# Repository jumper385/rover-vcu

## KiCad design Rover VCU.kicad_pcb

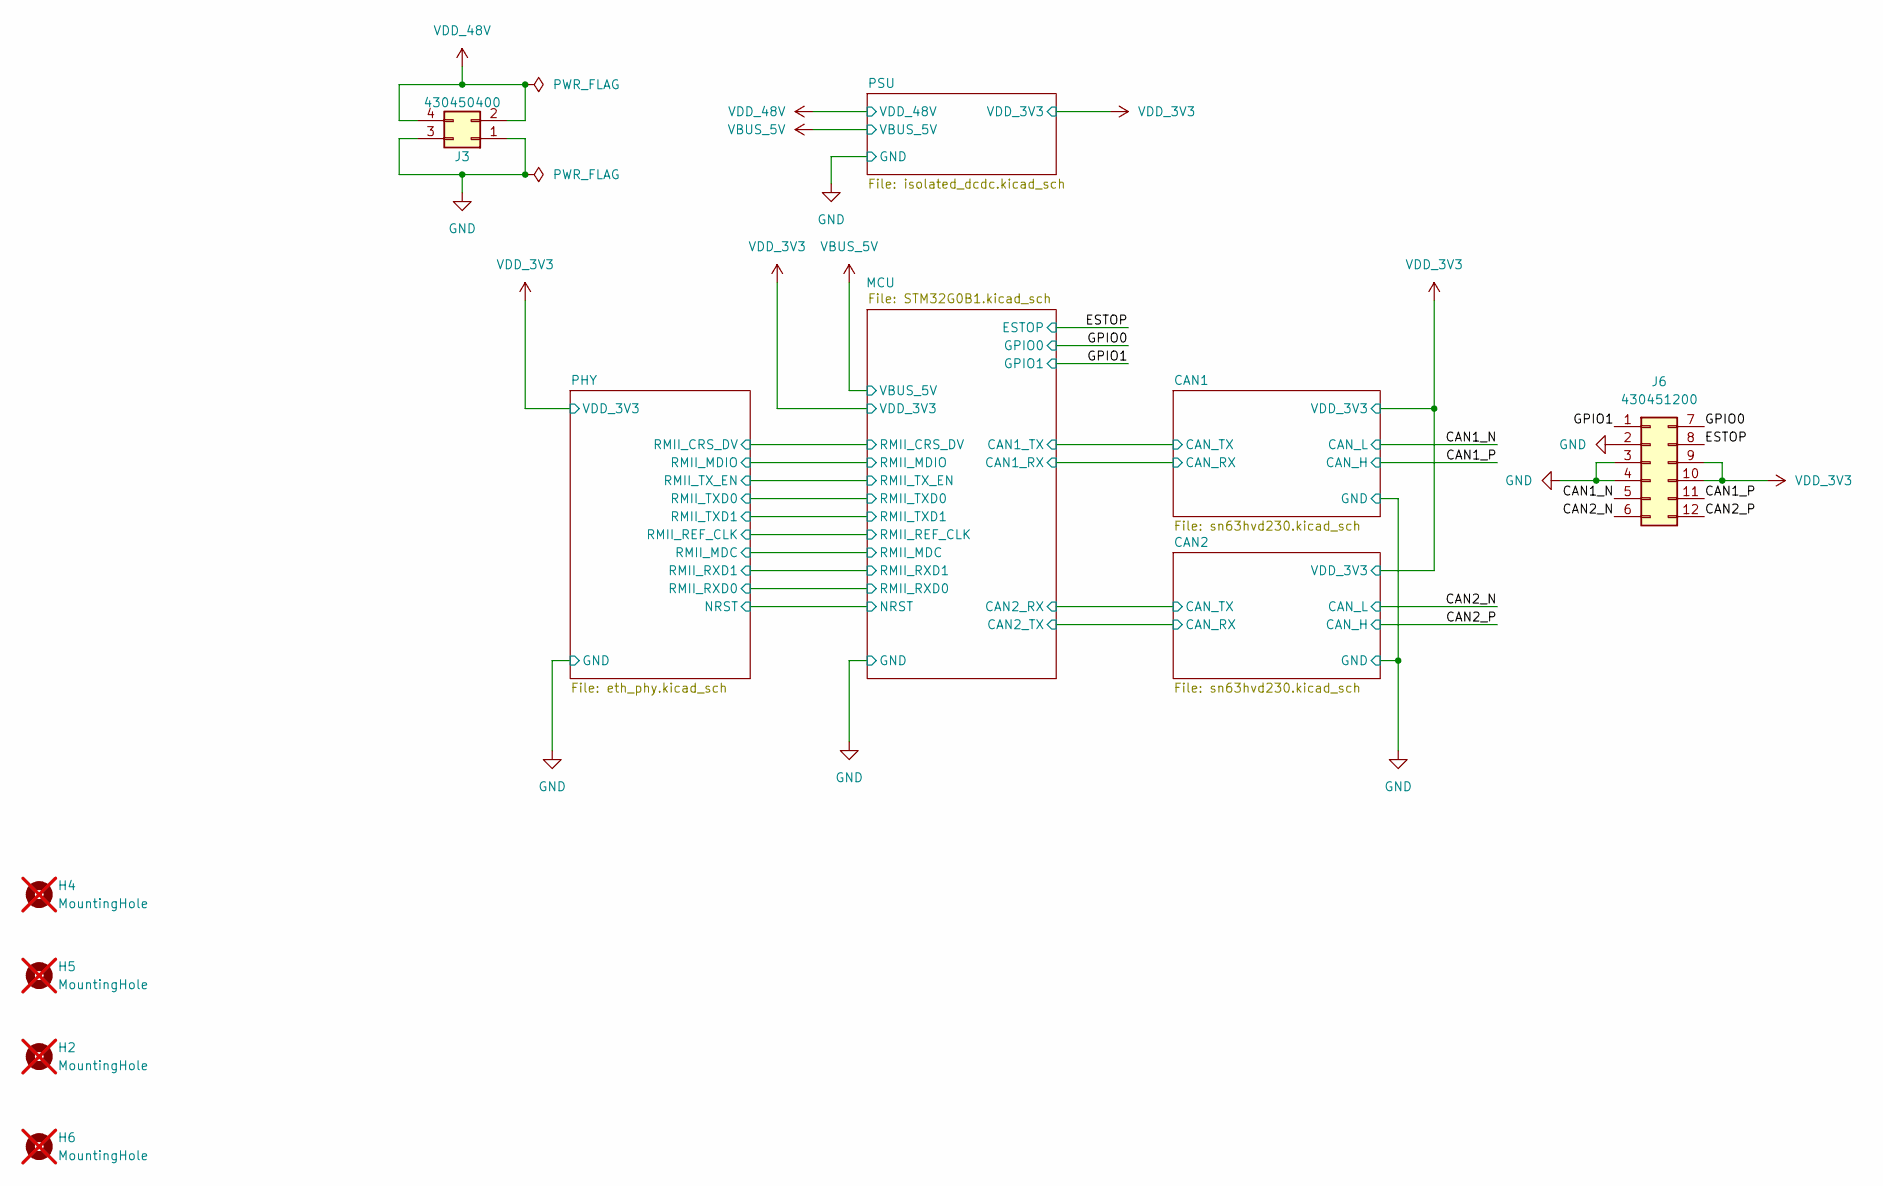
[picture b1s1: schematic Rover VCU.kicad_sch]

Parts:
H2, H4, H5, H6: MountingHole; MountingHole_3.2mm_M3; not fitted
J3: 430450400; Molex_Micro-Fit_3.0_43045-0400_2x02_P3.00mm_Horizontal; MFR_PN1 430450400; JLC_PN C122413
J6: 430451200; Molex_Micro-Fit_3.0_43045-1200_2x06_P3.00mm_Horizontal; MFR_PN1 430451200; JLC_PN C277636

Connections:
/CAN1_N: J6.5; also elsewhere on the board
/CAN1_P: J6.11; also elsewhere on the board
/CAN2_N: J6.6; also elsewhere on the board
/CAN2_P: J6.12; also elsewhere on the board
/ESTOP: J6.8; also elsewhere on the board
/GPIO0: J6.7; also elsewhere on the board
/GPIO1: J6.1; also elsewhere on the board
/VDD_3V3: J6.9, J6.10; also elsewhere on the board
/VDD_48V: J3.2, J3.4; also elsewhere on the board
GND: J3.1, J3.3, J6.2, J6.3, J6.4; also elsewhere on the board

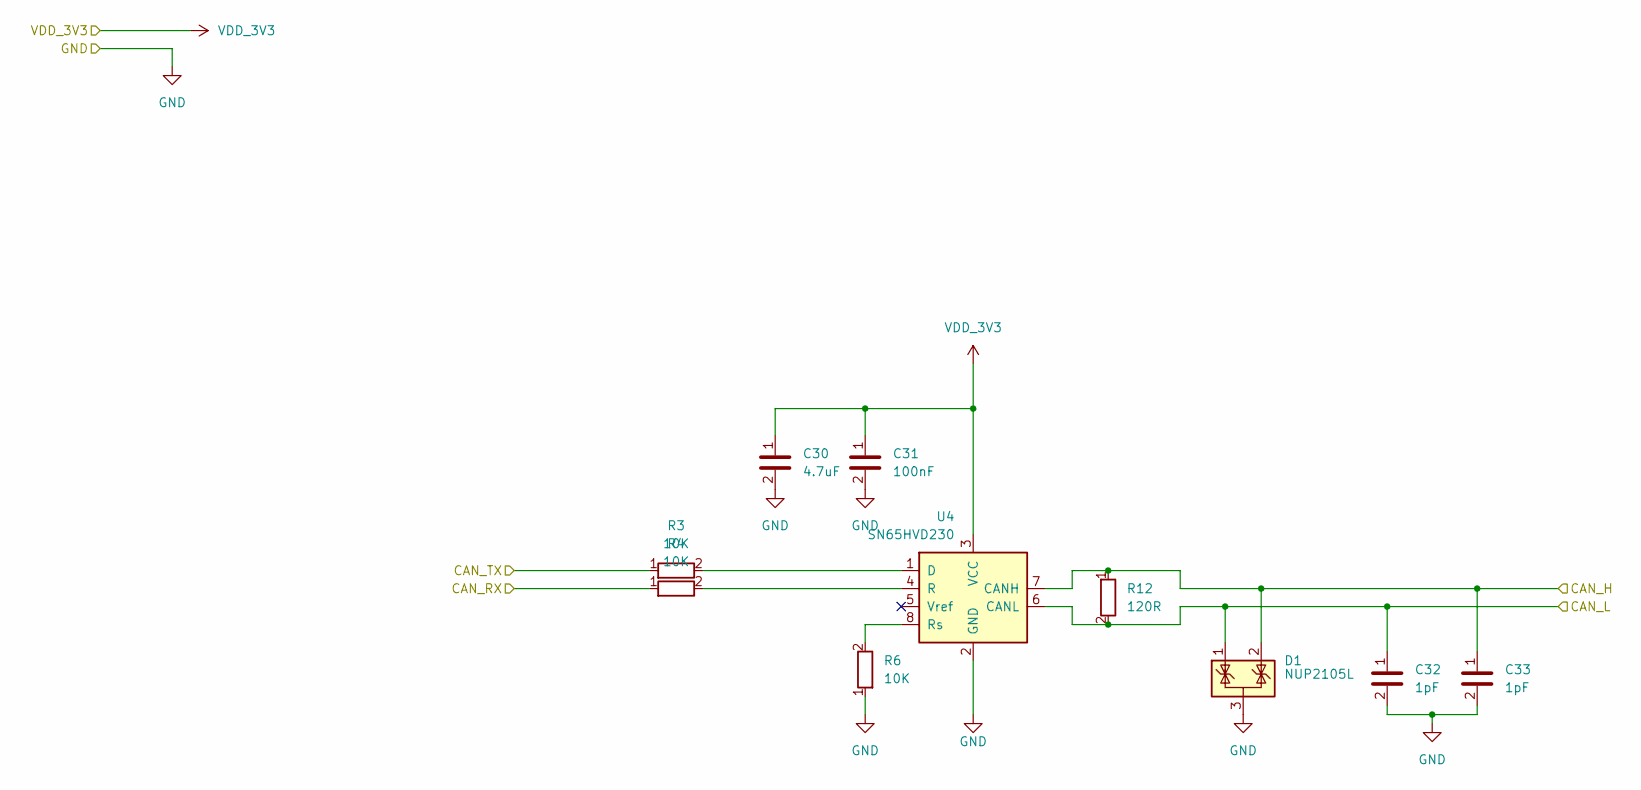
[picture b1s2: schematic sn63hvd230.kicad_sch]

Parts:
C30: 4.7uF; C_0402; Voltage Rating 10V; MFR_PN1 CL05A475MP5NRNC; JLC_PN C23733
C31: 100nF; C_0402; Voltage Rating 16V; MFR_PN1 CL05B104KO5NNNC; JLC_PN C1525
C32, C33: 1pF; C_0402; Voltage Rating 50V; MFR_PN1 0402CG1R0C500NT; JLC_PN C1550
D1: NUP2105L; SOT-23; MFR_PN1 NUP2105LT1G; JLC_PN C20617923
R3, R4, R6: 10K; R_0402; JLC_PN C25744
R12: 120R; R_0402; MFR_PN1 0402WGF1200TCE; JLC_PN C25079
U4: SN65HVD230; SOIC-8_3.9x4.9mm_P1.27mm; MFR_PN1 SN65HVD230DR; JLC_PN C12084

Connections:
/CAN1_N: C32.1, D1.1 (K), R12.2, U4.6 (CANL); also elsewhere on the board
/CAN1_P: C33.1, D1.2 (K), R12.1, U4.7 (CANH); also elsewhere on the board
/MCU/CAN1_RX: R4.1; also elsewhere on the board
/MCU/CAN1_TX: R3.1; also elsewhere on the board
/VDD_3V3: C30.1, C31.1, U4.3 (VCC); also elsewhere on the board
GND: C30.2, C31.2, C32.2, C33.2, D1.3 (A), R6.1, U4.2 (GND); also elsewhere on the board
unnamed: R3.2, U4.1 (D)
unnamed: R4.2, U4.4 (R)
unnamed: R6.2, U4.8 (Rs)

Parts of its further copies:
C34: 4.7uF; C_0402; Voltage Rating 10V; MFR_PN1 CL05A475MP5NRNC; JLC_PN C23733
C35: 100nF; C_0402; Voltage Rating 16V; MFR_PN1 CL05B104KO5NNNC; JLC_PN C1525
C36, C37: 1pF; C_0402; Voltage Rating 50V; MFR_PN1 0402CG1R0C500NT; JLC_PN C1550
D2: NUP2105L; SOT-23; MFR_PN1 NUP2105LT1G; JLC_PN C20617923
R7, R8, R9: 10K; R_0402; JLC_PN C25744
R13: 120R; R_0402; MFR_PN1 0402WGF1200TCE; JLC_PN C25079
U5: SN65HVD230; SOIC-8_3.9x4.9mm_P1.27mm; MFR_PN1 SN65HVD230DR; JLC_PN C12084

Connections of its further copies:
/CAN2_N: C36.1, D2.1 (K), R13.2, U5.6 (CANL); also elsewhere on the board
/CAN2_P: C37.1, D2.2 (K), R13.1, U5.7 (CANH); also elsewhere on the board
/MCU/CAN2_RX: R7.1; also elsewhere on the board
/MCU/CAN2_TX: R8.1; also elsewhere on the board
/VDD_3V3: C34.1, C35.1, U5.3 (VCC); also elsewhere on the board
GND: C34.2, C35.2, C36.2, C37.2, D2.3 (A), R9.1, U5.2 (GND); also elsewhere on the board
unnamed: R7.2, U5.1 (D)
unnamed: R8.2, U5.4 (R)
unnamed: R9.2, U5.8 (Rs)

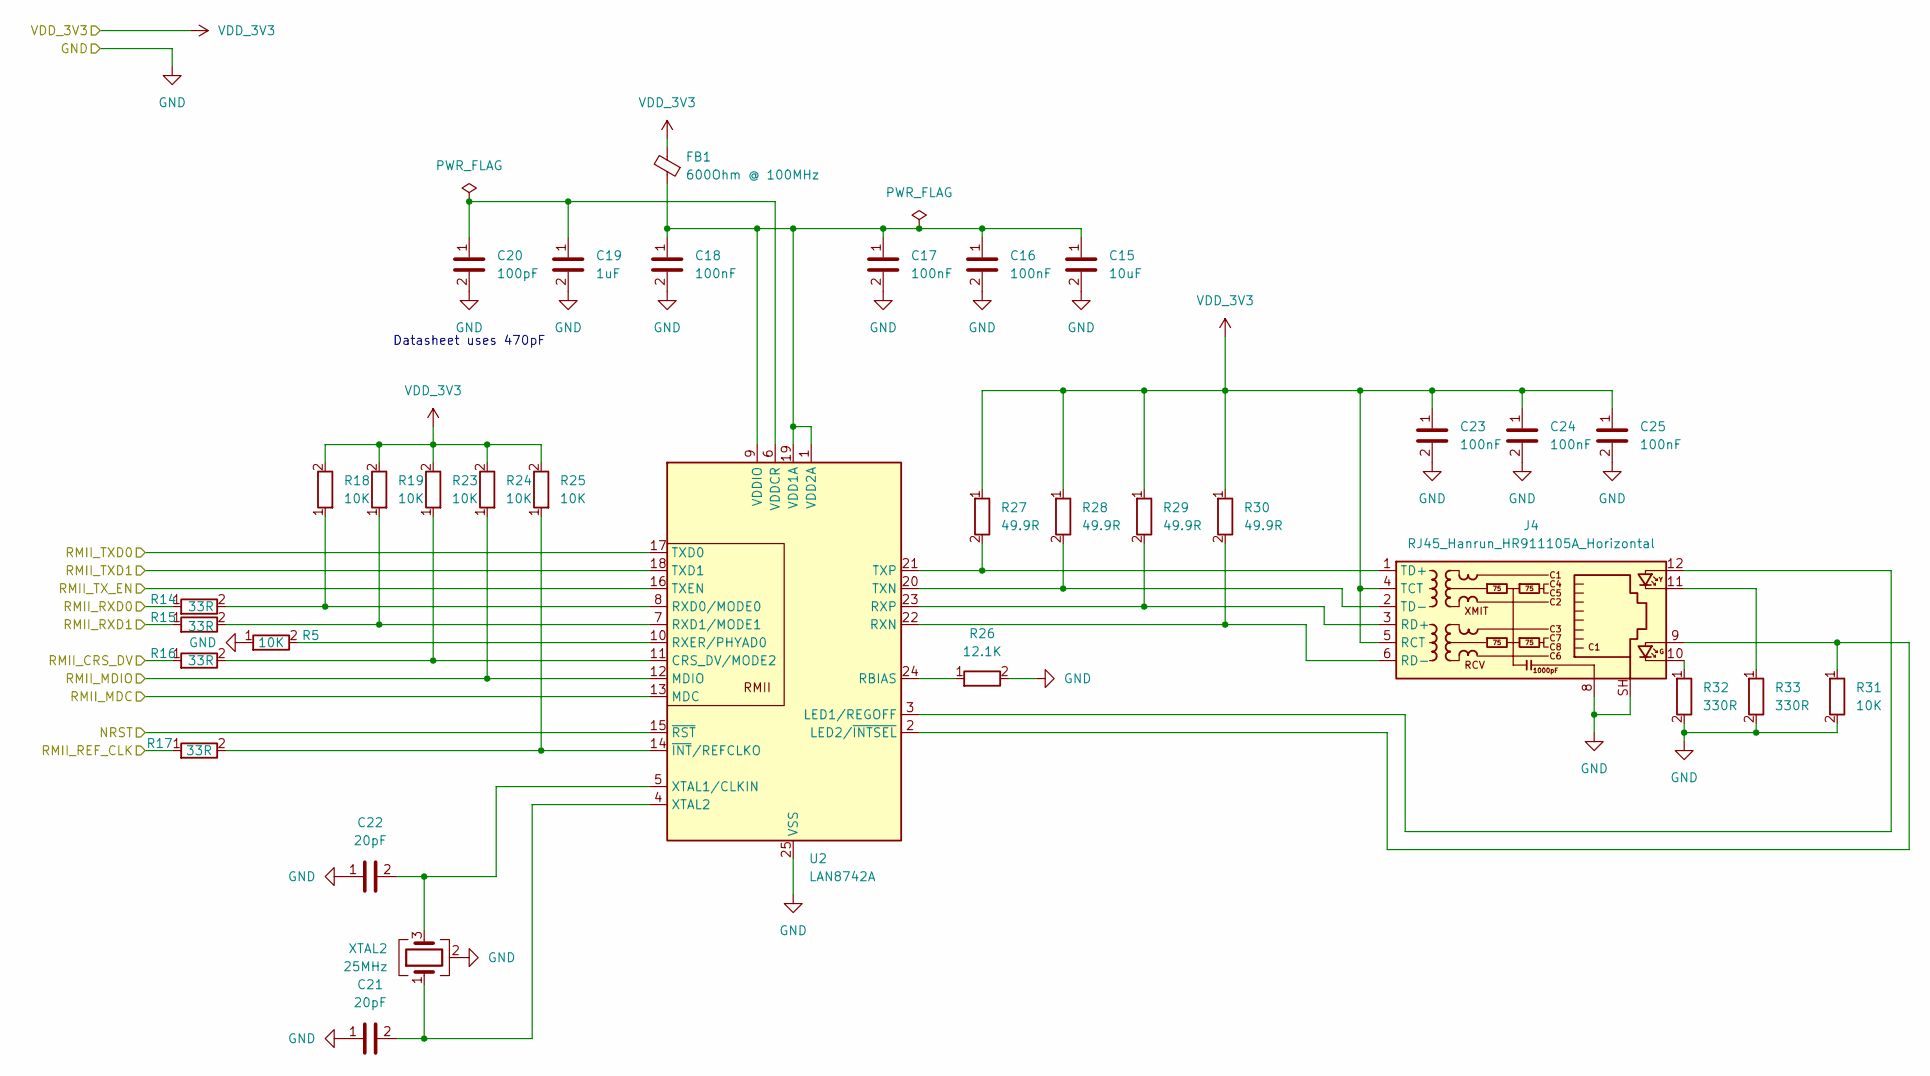
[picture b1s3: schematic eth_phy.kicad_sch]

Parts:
C15: 10uF; C_0402; Voltage Rating 6.3V; MFR_PN1 CL05A106MQ5NUNC; JLC_PN C15525
C16, C17, C18, C23, C24, C25: 100nF; C_0402; Voltage Rating 16V; MFR_PN1 CL05B104KO5NNNC; JLC_PN C1525
C19: 1uF; C_0402; Voltage Rating 25V; MFR_PN1 CL05A105KA5NQNC; JLC_PN C52923
C20: 100pF; C_0402; Voltage Rating 50V; MFR_PN1 0402CG101J500NT; JLC_PN C1546
C21, C22: 20pF; C_0402; Voltage Rating 50V; MFR_PN1 0402CG200J500NT; JLC_PN C1554
FB1: 600Ohm @ 100MHz; C_0603_1608Metric; MFR_PN1 BLM18KG601SH1D; JLC_PN C1002
J4: RJ45_Hanrun_HR911105A_Horizontal; MFR_PN1 HR911105A; JLC_PN C12074
R5, R18, R19, R23, R24, R25, R31: 10K; R_0402; JLC_PN C25744
R14, R15, R16, R17: 33R; R_0402; JLC_PN C25105
R26: 12.1K; R_0402; MFR_PN1 0805W8F1212T5E; JLC_PN C17431
R27, R28, R29, R30: 49.9R; R_0402; JLC_PN C25120
R32, R33: 330R; R_0402; JLC_PN C25104
U2: LAN8742A; VQFN-24-1EP_4x4mm_P0.5mm_EP2.5x2.5mm_ThermalVias; MFR_PN1 LAN8742AI-CZ-TR; JLC_PN C621425
XTAL2: 25MHz; Crystal_SMD_3225-4Pin_3.2x2.5mm; MFR_PN1 X322525MOB4SI; JLC_PN C9006

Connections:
/MCU/NRST: U2.15 (~RST); also elsewhere on the board
/MCU/RMII_CRS_DV: R16.1; also elsewhere on the board
/MCU/RMII_MDC: U2.13 (MDC); also elsewhere on the board
/MCU/RMII_MDIO: R24.1, U2.12 (MDIO); also elsewhere on the board
/MCU/RMII_REF_CLK: R17.1; also elsewhere on the board
/MCU/RMII_RXD0: R14.1; also elsewhere on the board
/MCU/RMII_RXD1: R15.1; also elsewhere on the board
/MCU/RMII_TXD0: U2.17 (TXD0); also elsewhere on the board
/MCU/RMII_TXD1: U2.18 (TXD1); also elsewhere on the board
/MCU/RMII_TX_EN: U2.16 (TXEN); also elsewhere on the board
/VDD_3V3: C23.1, C24.1, C25.1, FB1.2, J4.4 (TCT), J4.5 (RCT), R18.2, R19.2, R23.2, R24.2, R25.2, R27.1, R28.1, R29.1, R30.1; also elsewhere on the board
GND: C15.2, C16.2, C17.2, C18.2, C19.2, C20.2, C21.1, C22.1, C23.2, C24.2, C25.2, J4.8, J4.SH, R5.1, R26.2, R31.2, R32.2, R33.2, U2.25 (VSS), XTAL2.2 (G), XTAL2.4 (G); also elsewhere on the board
unnamed: J4.10, R32.1
unnamed: J4.11, R33.1
unnamed: J4.3 (RD+), R29.2, U2.23 (RXP)
unnamed: J4.6 (RD-), R30.2, U2.22 (RXN)
unnamed: J4.1 (TD+), R27.2, U2.21 (TXP)
unnamed: J4.2 (TD-), R28.2, U2.20 (TXN)
unnamed: R16.2, R23.1, U2.11 (CRS_DV/MODE2)
unnamed: J4.12, U2.3 (LED1/REGOFF)
unnamed: J4.9, R31.1, U2.2 (LED2/~INTSEL)
unnamed: R26.1, U2.24 (RBIAS)
unnamed: R14.2, R18.1, U2.8 (RXD0/MODE0)
unnamed: R15.2, R19.1, U2.7 (RXD1/MODE1)
unnamed: R5.2, U2.10 (RXER/PHYAD0)
unnamed: C15.1, C16.1, C17.1, C18.1, FB1.1, U2.1 (VDD2A), U2.9 (VDDIO), U2.19 (VDD1A)
unnamed: C19.1, C20.1, U2.6 (VDDCR)
unnamed: C22.2, U2.5 (XTAL1/CLKIN), XTAL2.3
unnamed: C21.2, U2.4 (XTAL2), XTAL2.1
unnamed: R17.2, R25.1, U2.14 (~INT/REFCLKO)

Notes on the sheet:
Datasheet uses 470pF

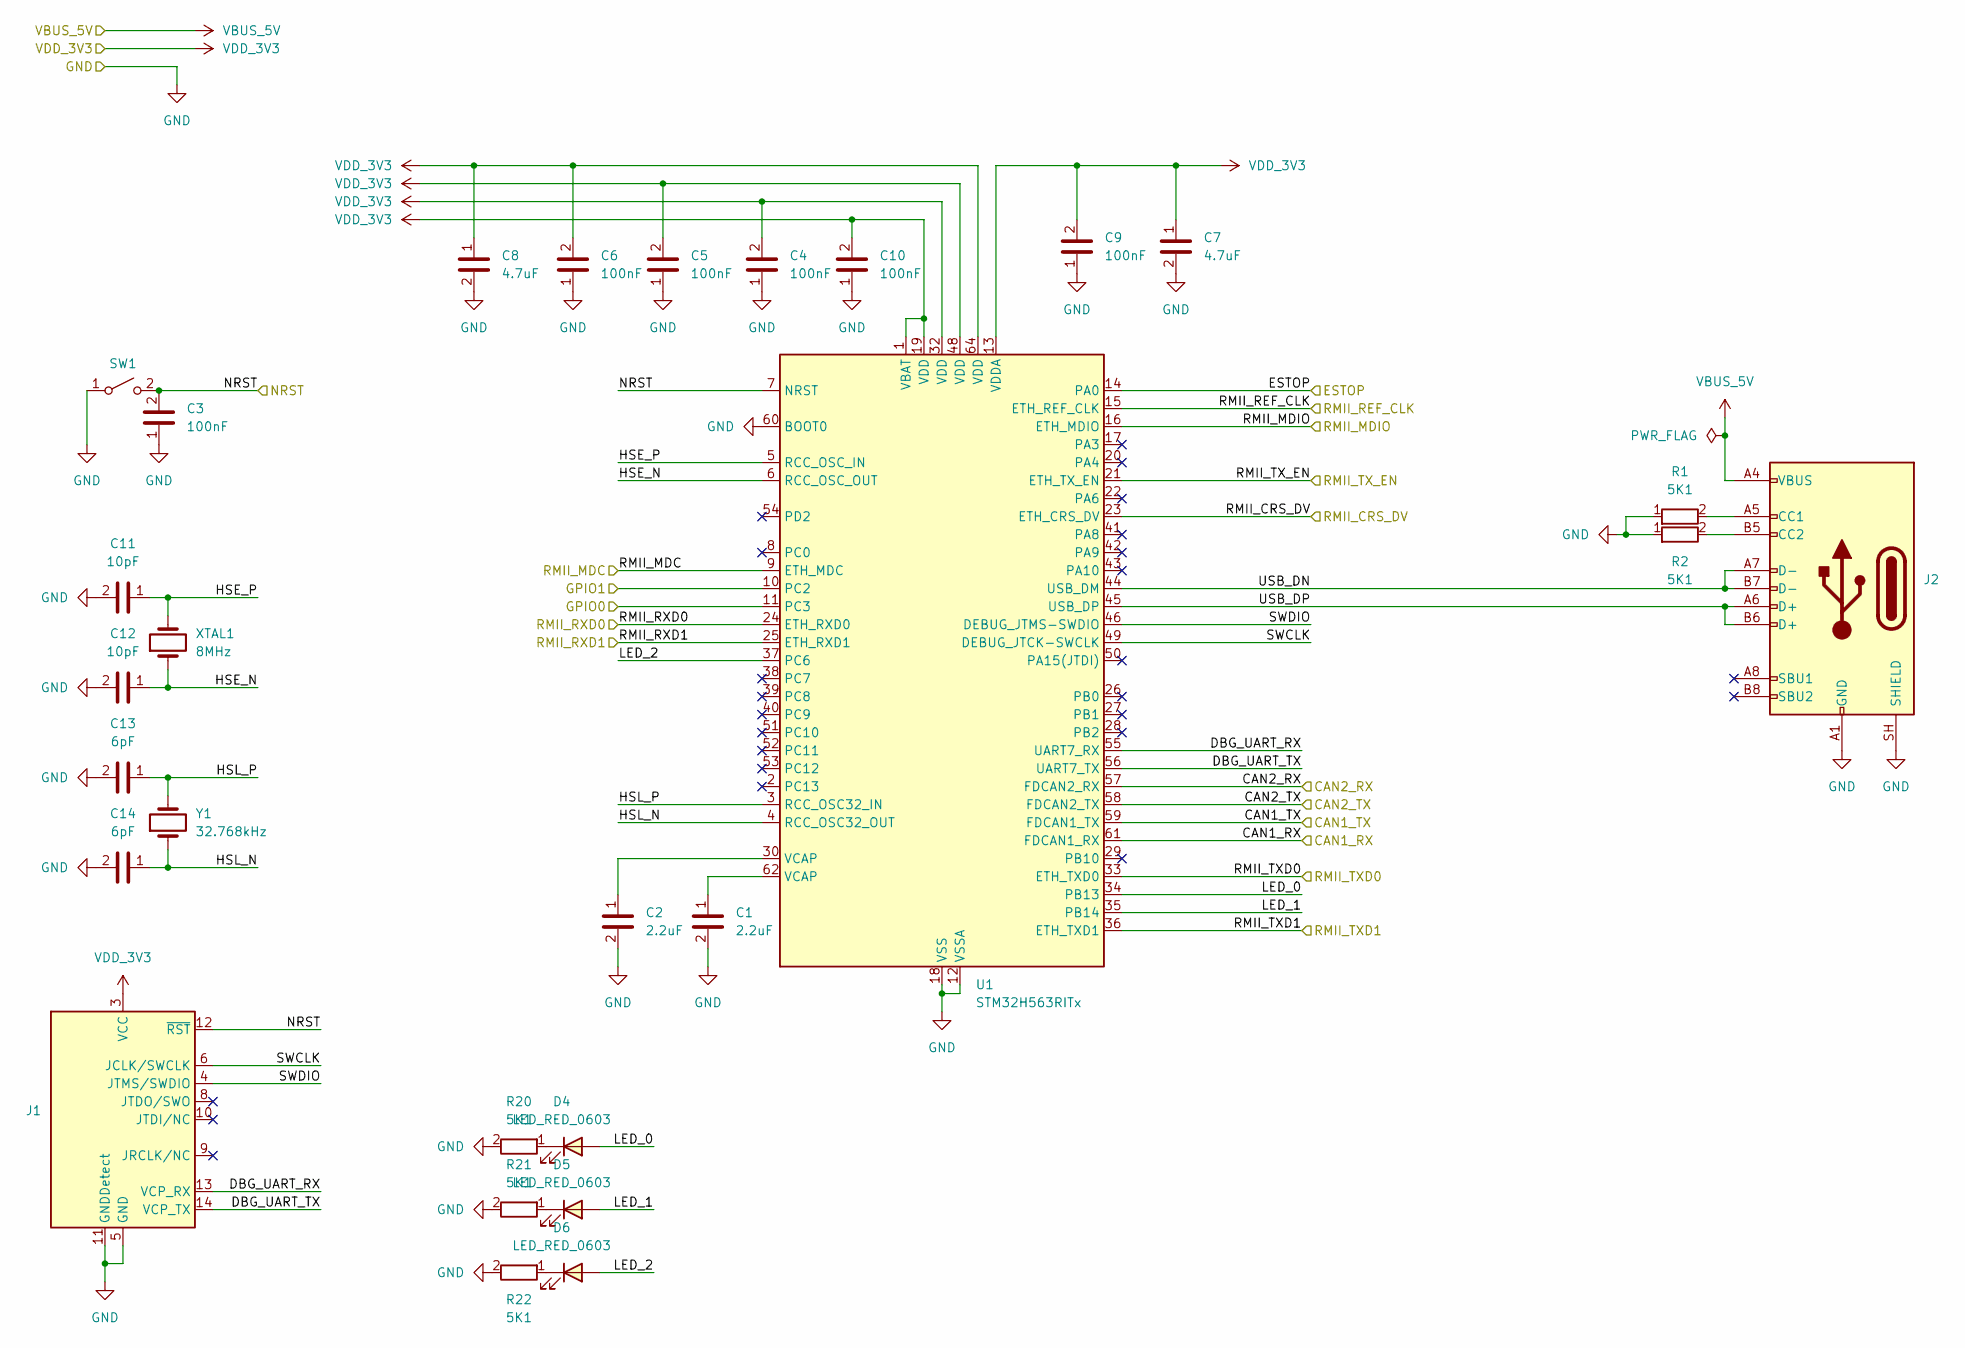
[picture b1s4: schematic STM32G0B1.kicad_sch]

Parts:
C1, C2: 2.2uF; C_0402; Voltage Rating 6.3V; MFR_PN1 CL05A225MQ5NSNC; JLC_PN C12530
C3, C4, C5, C6, C9, C10: 100nF; C_0402; Voltage Rating 16V; MFR_PN1 CL05B104KO5NNNC; JLC_PN C1525
C7, C8: 4.7uF; C_0402; Voltage Rating 10V; MFR_PN1 CL05A475MP5NRNC; JLC_PN C23733
C11, C12: 10pF; C_0402; Voltage Rating 50V; MFR_PN1 CL05C100JB5NNNC; JLC_PN C32949
C13, C14: 6pF; C_0402; Voltage Rating 50V; MFR_PN1 0402CG6R0C500NT; JLC_PN C30274
D4, D5, D6: LED_RED_0603; LED_0603_1608Metric; MFR_PN1 IN-S63FTHIR; JLC_PN C2286
J1: Conn_ST_STDC14; PinHeader_2x07_P1.27mm_Vertical_SMD; MFR_PN1 3220-14-0100-00; JLC_PN C27985148
J2: USB4105-GF-A; USB_C_Receptacle_GCT_USB4105-xx-A_16P_TopMnt_Horizontal; MFR_PN1 USB4105-GF-A; JLC_PN C393939
R1, R2, R20, R21, R22: 5K1; R_0402; JLC_PN C25905
SW1: TS-1088-AR02016; SW_SPST_TS-1088-xR020; MFR_PN1 C720477
U1: STM32H563RITx; LQFP-64_10x10mm_P0.5mm; JLC_PN C20619634
XTAL1: 8MHz; Crystal_SMD_5032-2Pin_5.0x3.2mm; MFR_PN1 X50328MSB2GI; JLC_PN C115962
Y1: 32.768kHz; Crystal_SMD_3215-2Pin_3.2x1.5mm; MFR_PN1 Q13FC13500004; JLC_PN C32346

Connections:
/ESTOP: U1.14 (PA0); also elsewhere on the board
/GPIO0: U1.11 (PC3); also elsewhere on the board
/GPIO1: U1.10 (PC2); also elsewhere on the board
/MCU/CAN1_RX: U1.61 (FDCAN1_RX); also elsewhere on the board
/MCU/CAN1_TX: U1.59 (FDCAN1_TX); also elsewhere on the board
/MCU/CAN2_RX: U1.57 (FDCAN2_RX); also elsewhere on the board
/MCU/CAN2_TX: U1.58 (FDCAN2_TX); also elsewhere on the board
/MCU/DBG_UART_RX: J1.13 (VCP_RX), U1.55 (UART7_RX)
/MCU/DBG_UART_TX: J1.14 (VCP_TX), U1.56 (UART7_TX)
/MCU/HSE_N: C12.1, U1.6 (RCC_OSC_OUT), XTAL1.1
/MCU/HSE_P: C11.1, U1.5 (RCC_OSC_IN), XTAL1.2
/MCU/HSL_N: C14.1, U1.4 (RCC_OSC32_OUT), Y1.1
/MCU/HSL_P: C13.1, U1.3 (RCC_OSC32_IN), Y1.2
/MCU/LED_0: D4.2 (A), U1.34 (PB13)
/MCU/LED_1: D5.2 (A), U1.35 (PB14)
/MCU/LED_2: D6.2 (A), U1.37 (PC6)
/MCU/NRST: C3.2, J1.12 (~RST), SW1.2 (B), U1.7 (NRST); also elsewhere on the board
/MCU/RMII_CRS_DV: U1.23 (ETH_CRS_DV); also elsewhere on the board
/MCU/RMII_MDC: U1.9 (ETH_MDC); also elsewhere on the board
/MCU/RMII_MDIO: U1.16 (ETH_MDIO); also elsewhere on the board
/MCU/RMII_REF_CLK: U1.15 (ETH_REF_CLK); also elsewhere on the board
/MCU/RMII_RXD0: U1.24 (ETH_RXD0); also elsewhere on the board
/MCU/RMII_RXD1: U1.25 (ETH_RXD1); also elsewhere on the board
/MCU/RMII_TXD0: U1.33 (ETH_TXD0); also elsewhere on the board
/MCU/RMII_TXD1: U1.36 (ETH_TXD1); also elsewhere on the board
/MCU/RMII_TX_EN: U1.21 (ETH_TX_EN); also elsewhere on the board
/MCU/SWCLK: J1.6 (JCLK/SWCLK), U1.49 (DEBUG_JTCK-SWCLK)
/MCU/SWDIO: J1.4 (JTMS/SWDIO), U1.46 (DEBUG_JTMS-SWDIO)
/MCU/USB_DN: J2.A7 (D-), J2.B7 (D-), U1.44 (USB_DM)
/MCU/USB_DP: J2.A6 (D+), J2.B6 (D+), U1.45 (USB_DP)
/VBUS_5V: J2.A4 (VBUS), J2.A9 (VBUS), J2.B4 (VBUS), J2.B9 (VBUS); also elsewhere on the board
/VDD_3V3: C4.2, C5.2, C6.2, C7.1, C8.1, C9.2, C10.2, J1.3 (VCC), U1.1 (VBAT), U1.13 (VDDA), U1.19 (VDD), U1.32 (VDD), U1.48 (VDD), U1.64 (VDD); also elsewhere on the board
GND: C1.2, C2.2, C3.1, C4.1, C5.1, C6.1, C7.2, C8.2, C9.1, C10.1, C11.2, C12.2, C13.2, C14.2, J1.5 (GND), J1.7 (GND), J1.11 (GNDDetect), J2.A1 (GND), J2.A12 (GND), J2.B1 (GND), J2.B12 (GND), J2.SH (SHIELD), R1.1, R2.1, R20.2, R21.2, R22.2, SW1.1 (A), U1.12 (VSSA), U1.18 (VSS), U1.31 (VSS), U1.47 (VSS), U1.60 (BOOT0), U1.63 (VSS); also elsewhere on the board
unnamed: C1.1, U1.62 (VCAP)
unnamed: C2.1, U1.30 (VCAP)
unnamed: D4.1 (K), R20.1
unnamed: D5.1 (K), R21.1
unnamed: D6.1 (K), R22.1
unnamed: J2.A5 (CC1), R1.2
unnamed: J2.B5 (CC2), R2.2

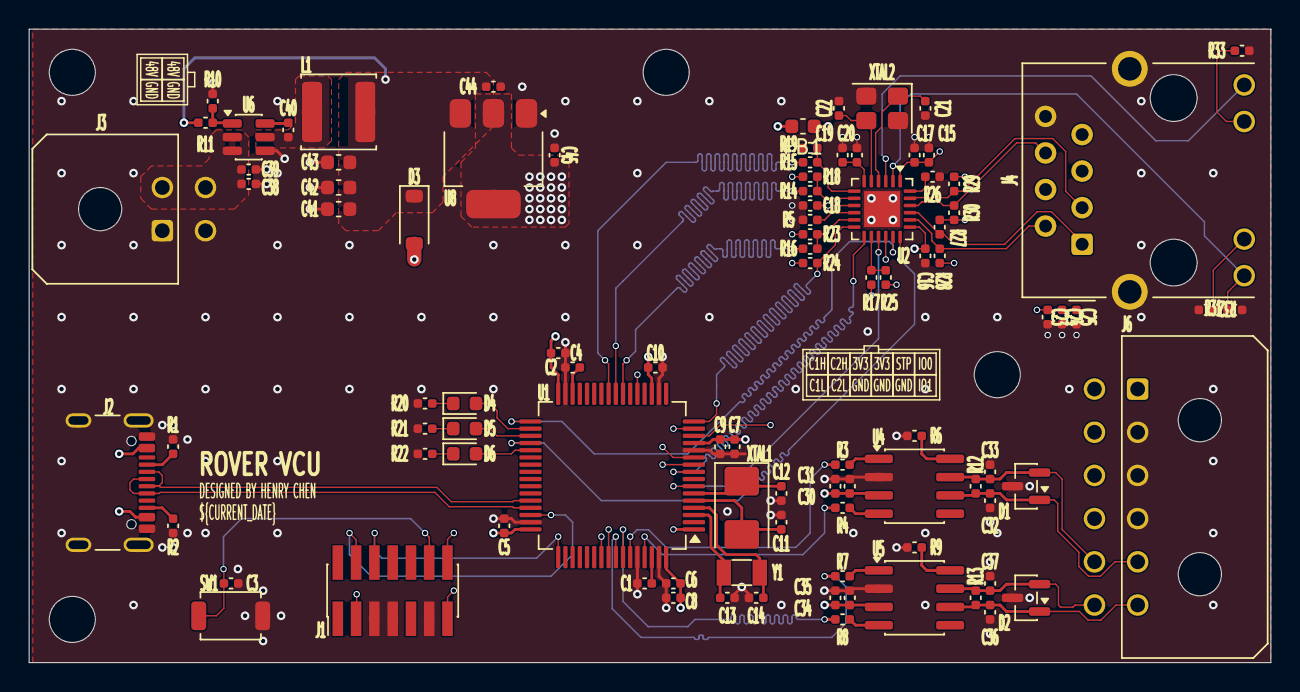
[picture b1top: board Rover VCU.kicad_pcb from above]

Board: 4 copper layers, 86.2 x 44.0 mm, 101 parts (0 on the bottom side), 73 nets.

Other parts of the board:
C38, C40: 100nF; C_0402
C39, C44, C45: 1uF; C_0402
C41, C42, C43: 22uF; C_0603_1608Metric
D3: B5819W; D_SOD-123
L1: 15uH; L_Sunlord_SWPA5040S
R10: 10K; R_0402
R11: 56K; R_0402
U6: LMR51610; SOT-23-6
U8: NCP1117-3.3_SOT223; SOT-223-3_TabPin2

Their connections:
/VBUS_5V: D3.2 (A); also elsewhere on the board
/VDD_3V3: C45.1, U8.2 (VO); also elsewhere on the board
/VDD_48V: C38.1, C39.1, U6.2 (EN), U6.3 (VIN); also elsewhere on the board
GND: C38.2, C39.2, C41.2, C42.2, C43.2, C44.2, C45.2, R10.2, U6.4 (GND), U8.1 (GND); also elsewhere on the board
unnamed: C41.1, C42.1, C43.1, C44.1, D3.1 (K), L1.2, R11.1, U8.3 (VI)
unnamed: C40.2, U6.6 (CB)
unnamed: R10.1, R11.2, U6.1 (FB)
unnamed: C40.1, L1.1, U6.5 (SW)

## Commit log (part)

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2026-06-03 added kicad lib submodule
2026-06-03 ci: added commitizen and github builds
2026-06-03 ci: added kibot
2026-06-03 feat: added mcu
2026-06-04 feat: added stm32h563
2026-06-07 feat: completed h63 implementation
2026-06-08 feat: added eth and can with
2026-06-08 feat: added can bus channels and psu
2026-06-08 ci: added pcb file for build complete
2026-06-08 ci: debug
2026-06-08 ci: kicad 10
2026-06-08 ci: fixing CI to generate outputs
2026-06-08 bump: version 0.0.1 → 0.1.0
2026-06-08 ci: bug fix on tar.gz file
2026-06-08 fix: adjusted PNs for PSU systems
2026-06-08 feat: added MVP routing implementation
2026-06-08 fix: centering board on layout
2026-06-08 bump: version 0.1.0 → 0.2.0
2026-06-08 ci: output shcemaitc too
2026-06-08 chore: updating Rover
2026-06-08 fix: cleaned up DRC and ERC's for major errors
2026-06-11 fix: adde more changes from excel checklist for eth phy
2026-06-11 bump: version 0.2.0 → 0.2.1
2026-06-12 fix: final polishes for MFR
2026-06-12 fix: added annotations and 3d models
2026-06-14 fix: updated 12pin connector footprint + fix drc and exposed vias
2026-06-14 bump: version 0.2.1 → 0.2.2
2026-06-15 fix: tiny fixes; adjusted pin names as check
2026-06-15 bump: version 0.2.2 → 0.2.3
2026-06-15 chore: updating lib
2026-06-16 fix: added leds to phy
2026-06-16 bump: version 0.2.3 → 0.2.4
2026-06-16 chore: update lib
